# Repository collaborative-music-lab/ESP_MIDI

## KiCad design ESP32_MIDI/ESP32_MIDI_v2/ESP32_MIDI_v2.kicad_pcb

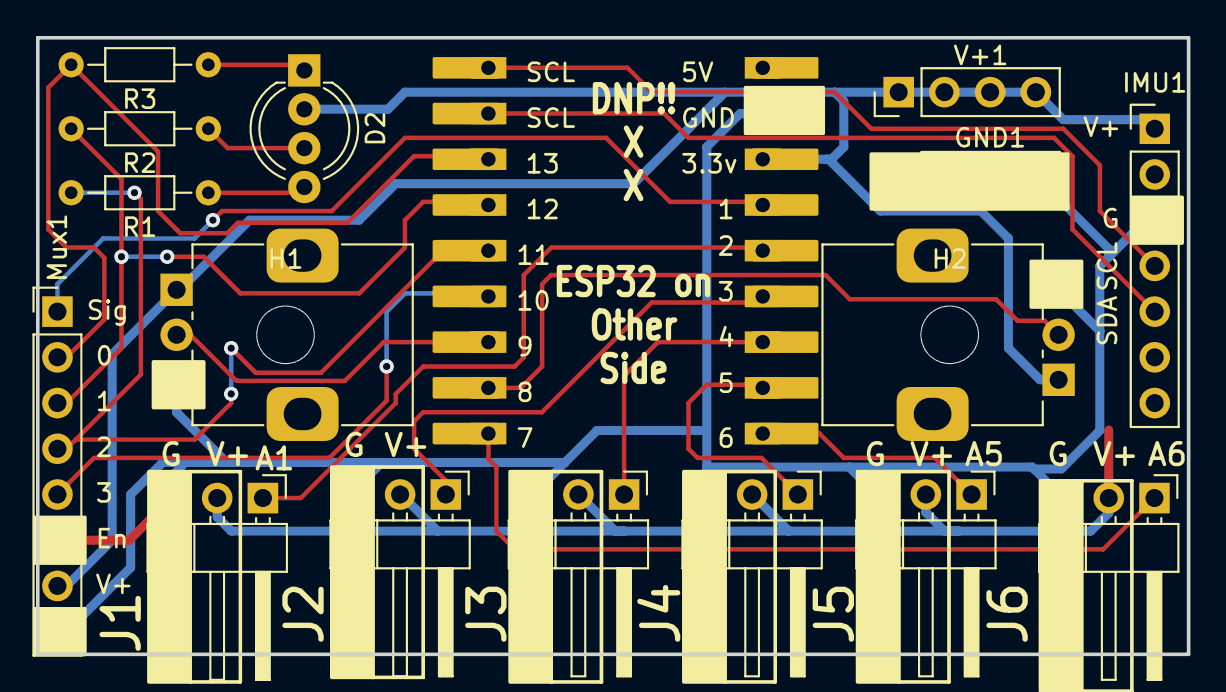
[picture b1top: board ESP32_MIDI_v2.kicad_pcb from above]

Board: 2 copper layers, 63.9 x 34.3 mm, 19 parts (1 on the bottom side), 20 nets.

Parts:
D2: LED_RAGB; LED_D5.0mm-4_RGB_Wide_Pins
GND1: Conn_01x04_Pin; PinHeader_1x04_P2.54mm_Vertical
H1, H2: MountingHole; MountingHole_3.2mm_M3
IMU1: Conn_01x07_Pin; PinHeader_1x07_P2.54mm_Vertical
J1, J2, J3, J4, J5, J6: Conn_01x03_Pin; PinHeader_1x03_P2.54mm_Horizontal
Mux1: Conn_01x08_Pin; PinHeader_1x08_P2.54mm_Vertical
R1, R2, R3: R; R_Axial_DIN0204_L3.6mm_D1.6mm_P7.62mm_Horizontal
RV1, RV2: R_Potentiometer; Potentiometer_Alps_RK09K_Single_Vertical
U2: Wifiduino-ESP32S3
V+1: Conn_01x04_Pin; PinHeader_1x04_P2.54mm_Vertical

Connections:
+3.3V: D2.2 (A), IMU1.1, J1.2, J2.2, J3.2, J4.2, J5.2, J6.2, Mux1.7, RV1.1, RV2.1, U2.3 (3V3), V+1.1, V+1.2, V+1.3, V+1.4
/A0: Mux1.1, U2.4 (GPIO1/ADC1_CH0)
/A1: J1.1, U2.5 (GPIO2/ADC1_CH1)
/A2: J2.1, U2.6 (GPIO3/ADC1_CH2)
/A3: J3.1, U2.7 (GPIO4/ADC1_CH3)
/A4: J4.1, U2.8 (GPIO5/ADC1_CH4)
/A5: J5.1, U2.9 (GPIO6/ADC1_CH5)
/A6: J6.1, U2.10 (GPIO7/ADC1_CH6)
/A7: RV2.2, U2.11 (GPIO8/ADC1_CH7)
/A8: RV1.2, U2.12 (GPIO9/ADC1_CH8)
/A9: Mux1.5, U2.13 (GPIO10/ADC1_CH9)
/D0: Mux1.4, R1.2, U2.14 (GPIO11/ADC2_CH0)
/D1: Mux1.3, R2.2, U2.15 (GPIO12/ADC2_CH1)
/D2: Mux1.2, R3.2, U2.16 (GPIO13/ADC2_CH2)
/SCL: IMU1.4, U2.18 (GPIO43/U0TXD)
/SDA: IMU1.5, U2.17 (GPIO44/U0RXD)
GND: GND1.1, GND1.2, GND1.3, GND1.4, IMU1.3, J1.3, J2.3, J3.3, J4.3, J5.3, J6.3, Mux1.6, Mux1.8, RV1.3, RV2.3, U2.2 (GND)
unnamed: D2.4 (BK), R1.1
unnamed: D2.3 (GK), R2.1
unnamed: D2.1 (RK), R3.1

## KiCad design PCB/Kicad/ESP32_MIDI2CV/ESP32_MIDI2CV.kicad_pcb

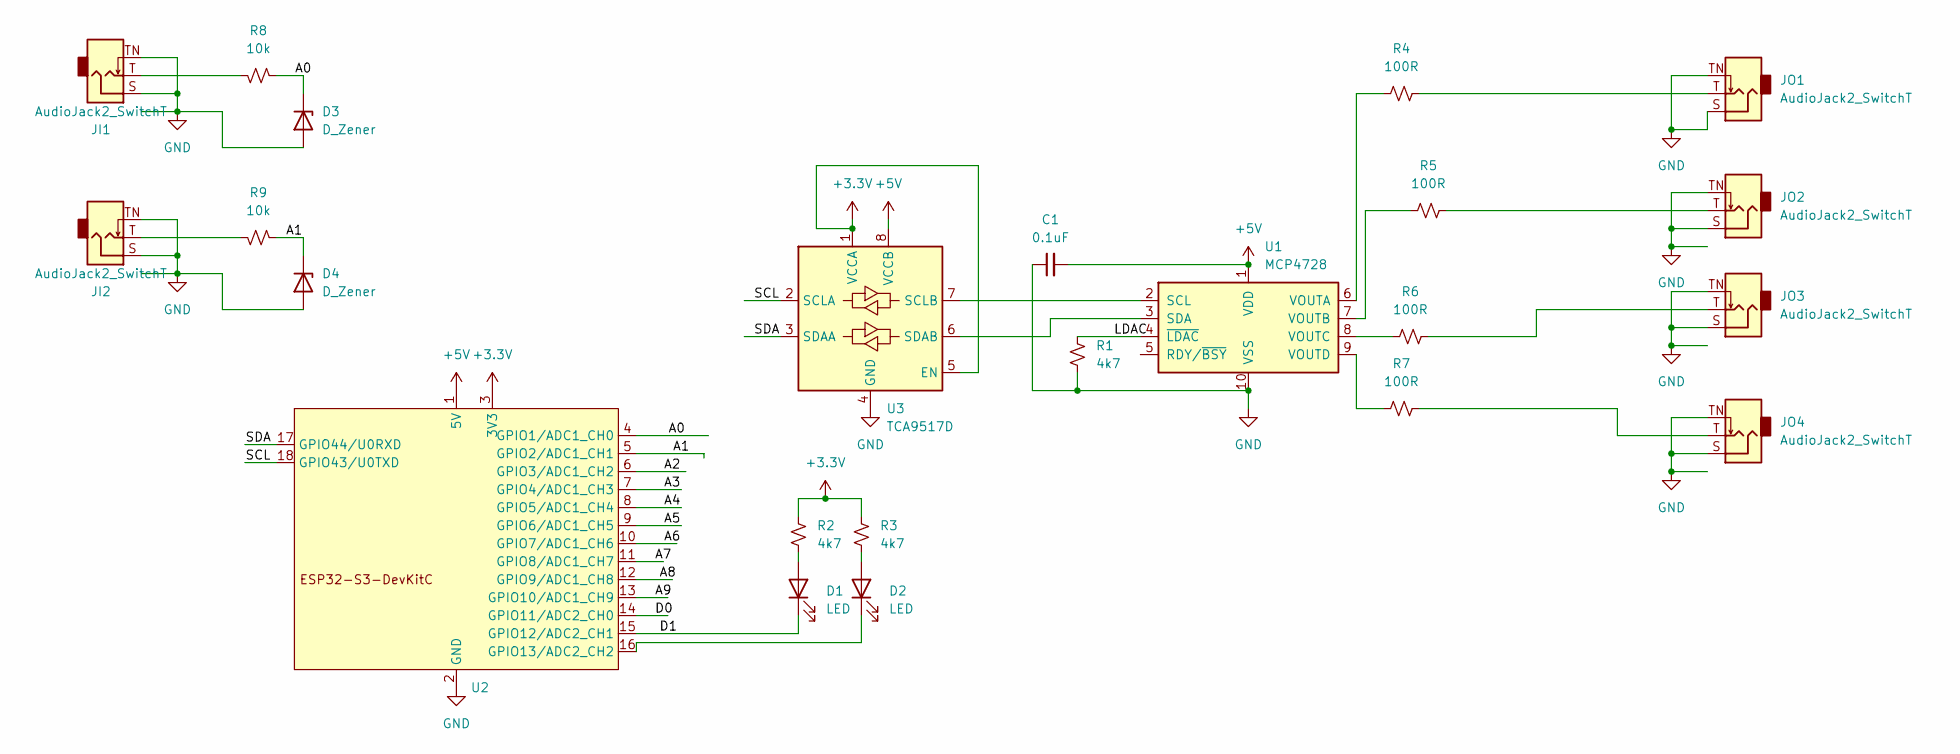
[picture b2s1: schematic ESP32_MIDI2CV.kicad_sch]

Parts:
C1: 0.1uF; C_Disc_D6.0mm_W2.5mm_P5.00mm
D1, D2: LED; LED_D3.0mm
D3, D4: D_Zener; D_DO-35_SOD27_P7.62mm_Horizontal
JI1, JI2: AudioJack2_SwitchT; Jack_3.5mm_QingPu_WQP-PJ398SM_Vertical_CircularHoles
JO1, JO2, JO3, JO4: AudioJack2_SwitchT; Jack_3.5mm_QingPu_WQP-PJ398SM_Vertical_CircularHoles
R1, R2, R3: 4k7; R_0805_2012Metric
R4, R5, R6, R7: 100R; R_0805_2012Metric
R8, R9: 10k; R_0805_2012Metric
U1: MCP4728; MSOP-10_3x3mm_P0.5mm
U2: Wifiduino-ESP32S3-SMD
U3: TCA9517D; SOIC-8_3.9x4.9mm_P1.27mm

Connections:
+3.3V: R2.1, R3.1, U2.3 (3V3), U3.1 (VCCA), U3.5 (EN)
+5V: C1.2, U1.1 (VDD), U2.1 (5V), U3.8 (VCCB)
/A0: D3.1 (K), R8.1, U2.4 (GPIO1/ADC1_CH0)
/A1: D4.1 (K), R9.1, U2.5 (GPIO2/ADC1_CH1)
/A2: U2.6 (GPIO3/ADC1_CH2)
/A3: U2.7 (GPIO4/ADC1_CH3)
/A4: U2.8 (GPIO5/ADC1_CH4)
/A5: U2.9 (GPIO6/ADC1_CH5)
/A6: U2.10 (GPIO7/ADC1_CH6)
/A7: U2.11 (GPIO8/ADC1_CH7)
/A8: U2.12 (GPIO9/ADC1_CH8)
/A9: U2.13 (GPIO10/ADC1_CH9)
/D0: U2.14 (GPIO11/ADC2_CH0)
/D1: D1.1 (K), U2.15 (GPIO12/ADC2_CH1)
/LDAC: R1.1, U1.4 (~LDAC)
/SCL: U2.18 (GPIO43/U0TXD), U3.2 (SCLA)
/SDA: U2.17 (GPIO44/U0RXD), U3.3 (SDAA)
GND: C1.1, D3.2 (A), D4.2 (A), JI1.S, JI1.TN, JI2.S, JI2.TN, JO1.S, JO1.TN, JO2.S, JO2.TN, JO3.S, JO3.TN, JO4.S, JO4.TN, R1.2, U1.10 (VSS), U2.2 (GND), U3.4 (GND)
unnamed: D1.2 (A), R2.2
unnamed: D2.2 (A), R3.2
unnamed: D2.1 (K), U2.16 (GPIO13/ADC2_CH2)
unnamed: JI1.T, R8.2
unnamed: JI2.T, R9.2
unnamed: JO1.T, R4.2
unnamed: JO2.T, R5.2
unnamed: JO3.T, R6.2
unnamed: JO4.T, R7.2
unnamed: U1.2 (SCL), U3.7 (SCLB)
unnamed: U1.3 (SDA), U3.6 (SDAB)
unnamed: R4.1, U1.6 (VOUTA)
unnamed: R5.1, U1.7 (VOUTB)
unnamed: R6.1, U1.8 (VOUTC)
unnamed: R7.1, U1.9 (VOUTD)

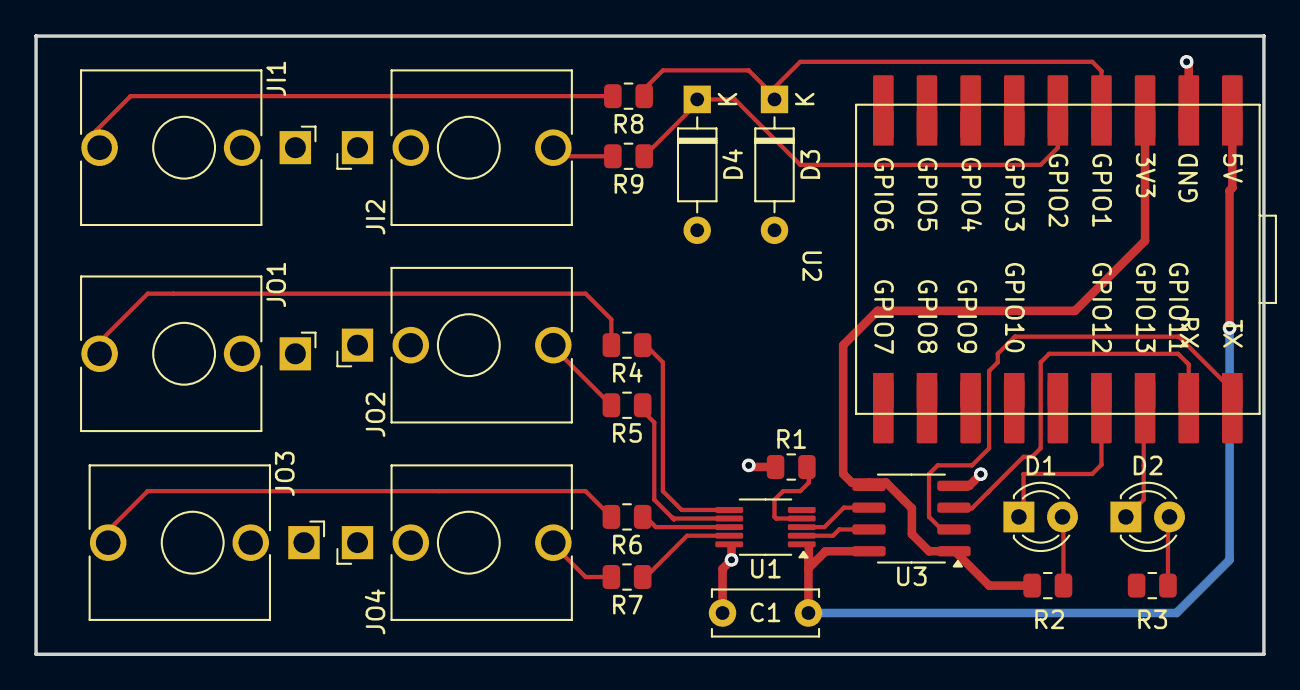
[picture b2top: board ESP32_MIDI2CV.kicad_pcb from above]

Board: 2 copper layers, 71.5 x 36.0 mm, 23 parts (0 on the bottom side), 24 nets.

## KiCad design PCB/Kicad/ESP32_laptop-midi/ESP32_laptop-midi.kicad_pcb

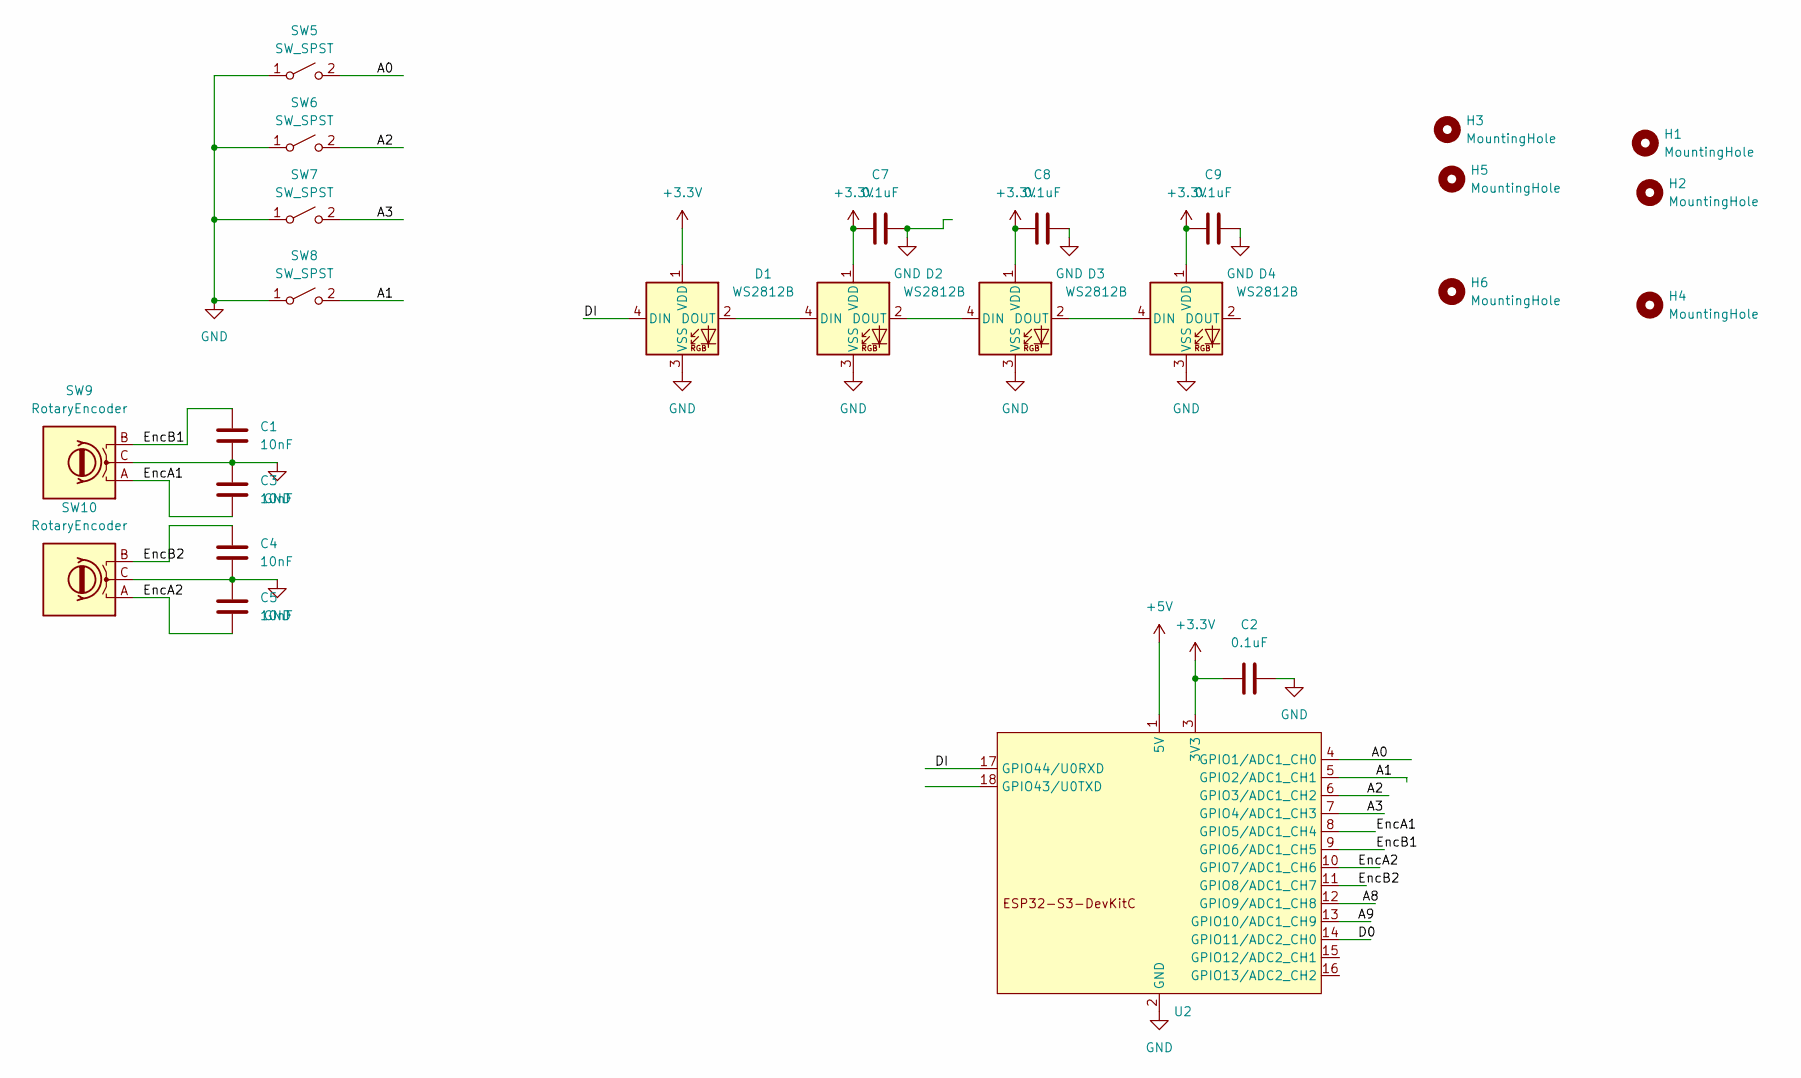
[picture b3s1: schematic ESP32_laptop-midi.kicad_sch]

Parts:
C1, C3, C4, C5: 10nF; C_0805_2012Metric_Pad1.18x1.45mm_HandSolder
C2, C7, C8, C9: 0.1uF; C_0805_2012Metric_Pad1.18x1.45mm_HandSolder
D1, D2, D3, D4: WS2812B; LED_WS2812B_PLCC4_5.0x5.0mm_P3.2mm
H1, H2, H3, H4, H5, H6: MountingHole; MountingHole_3.2mm_M3
SW5, SW6, SW7, SW8: SW_SPST; SW_Cherry_MX_1.00u_PCB
SW9, SW10: RotaryEncoder; EC10E1220505_AAL
U2: Wifiduino-ESP32S3-SMD

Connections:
+3.3V: C2.2, C7.2, C8.2, C9.2, D1.1 (VDD), D2.1 (VDD), D3.1 (VDD), D4.1 (VDD), U2.3 (3V3)
+5V: U2.1 (5V)
/A0: SW5.2 (B), U2.4 (GPIO1/ADC1_CH0)
/A1: SW8.2 (B), U2.5 (GPIO2/ADC1_CH1)
/A2: SW6.2 (B), U2.6 (GPIO3/ADC1_CH2)
/A3: SW7.2 (B), U2.7 (GPIO4/ADC1_CH3)
/A8: U2.12 (GPIO9/ADC1_CH8)
/A9: U2.13 (GPIO10/ADC1_CH9)
/D0: U2.14 (GPIO11/ADC2_CH0)
/DI: D1.4 (DIN), U2.17 (GPIO44/U0RXD)
/EncA1: C3.2, SW9.A, U2.8 (GPIO5/ADC1_CH4)
/EncA2: C5.2, SW10.A, U2.10 (GPIO7/ADC1_CH6)
/EncB1: C1.1, SW9.B, U2.9 (GPIO6/ADC1_CH5)
/EncB2: C4.1, SW10.B, U2.11 (GPIO8/ADC1_CH7)
GND: C1.2, C2.1, C3.1, C4.2, C5.1, C7.1, C8.1, C9.1, D1.3 (VSS), D2.3 (VSS), D3.3 (VSS), D4.3 (VSS), SW5.1 (A), SW6.1 (A), SW7.1 (A), SW8.1 (A), SW9.C, SW10.C, U2.2 (GND)
unnamed: D1.2 (DOUT), D2.4 (DIN)
unnamed: D2.2 (DOUT), D3.4 (DIN)
unnamed: D3.2 (DOUT), D4.4 (DIN)

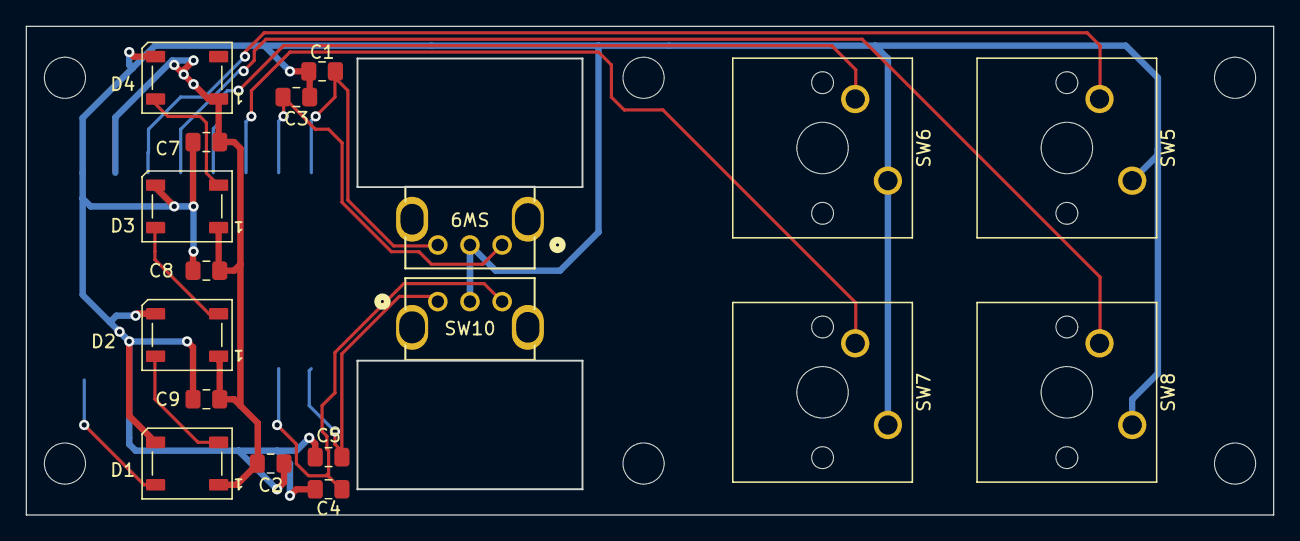
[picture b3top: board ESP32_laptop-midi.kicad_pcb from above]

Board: 2 copper layers, 97.0 x 38.0 mm, 25 parts (1 on the bottom side), 14 nets.

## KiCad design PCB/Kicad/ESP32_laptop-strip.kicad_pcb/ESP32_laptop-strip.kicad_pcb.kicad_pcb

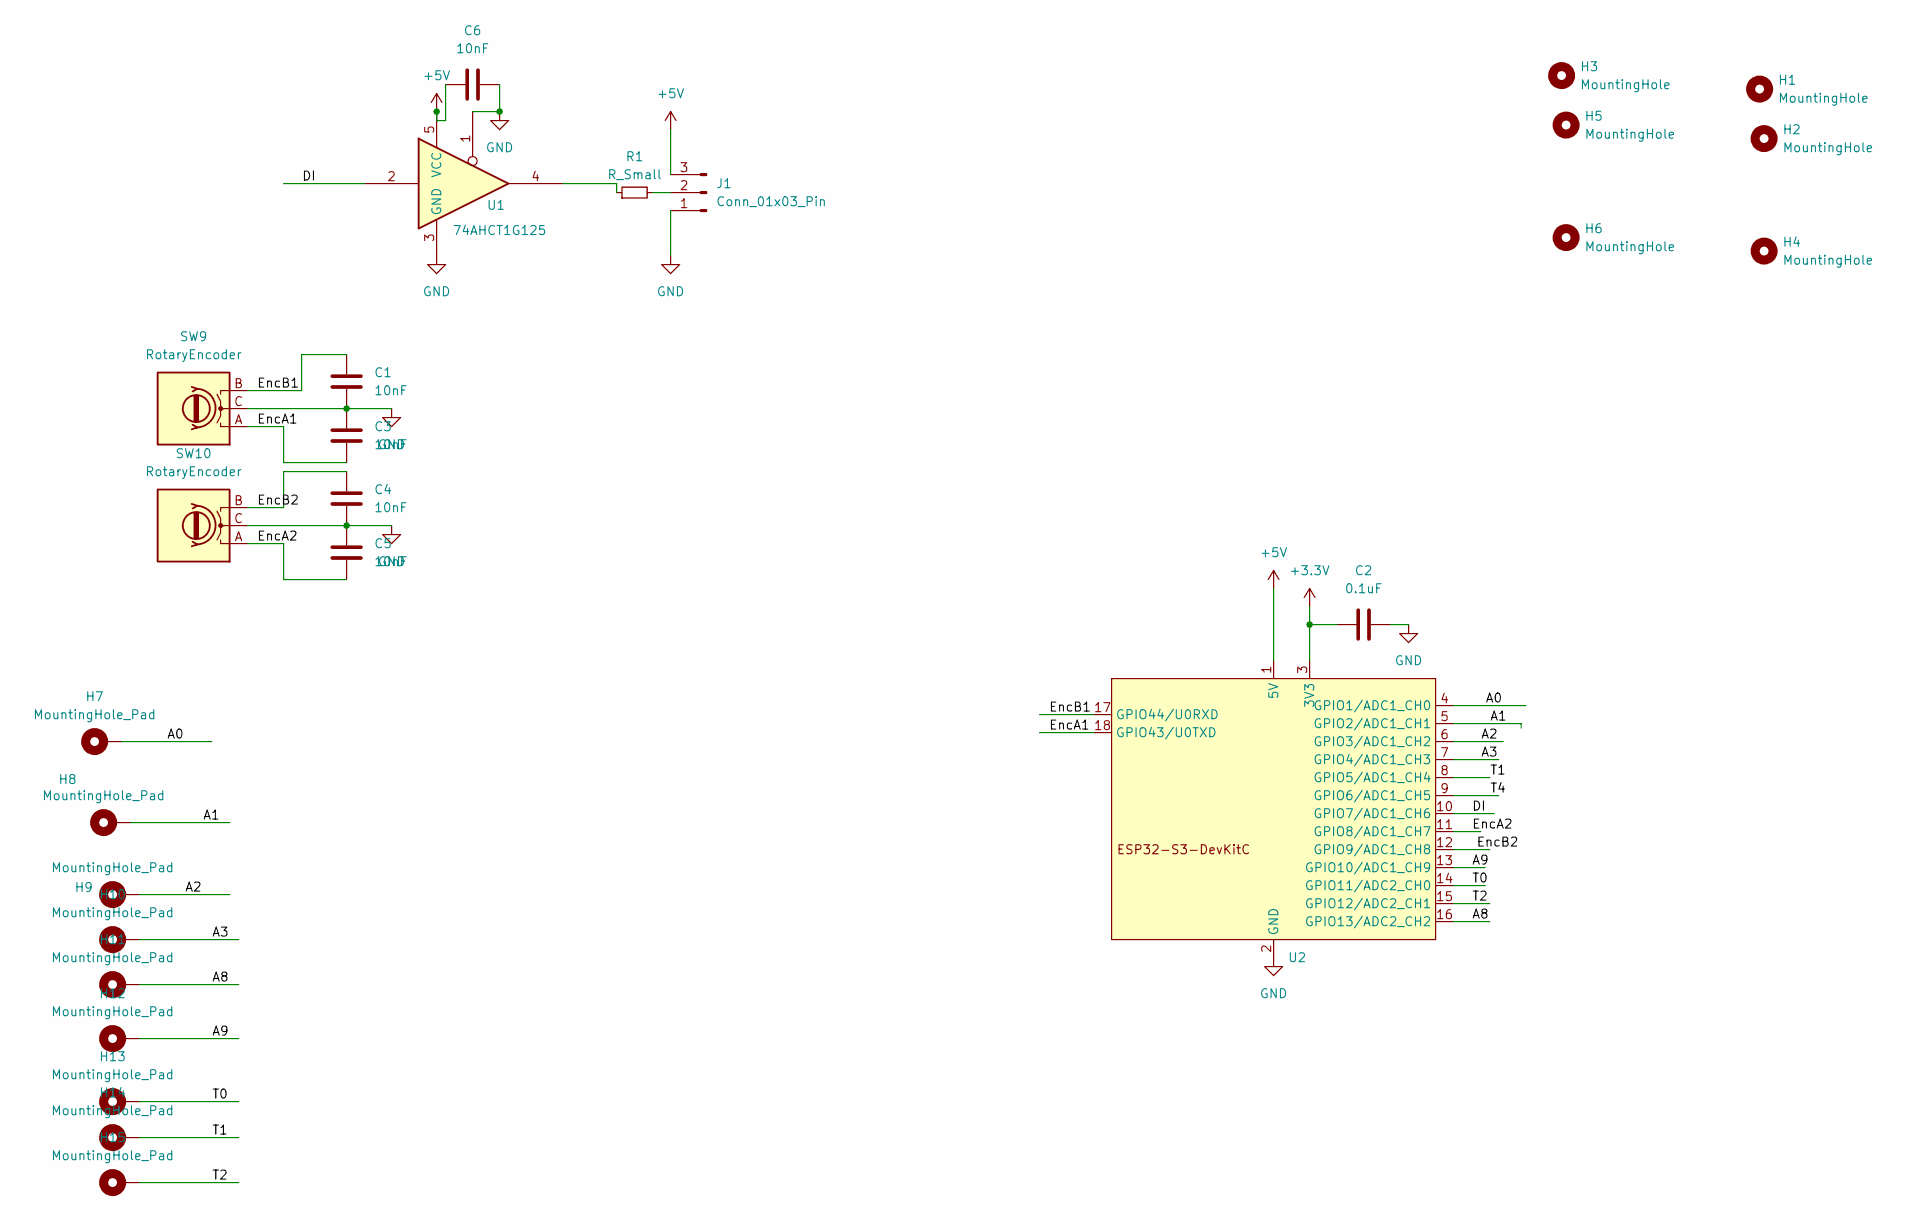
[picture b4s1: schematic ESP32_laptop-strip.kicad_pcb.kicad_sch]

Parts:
C1, C3, C4, C5, C6: 10nF; C_0805_2012Metric_Pad1.18x1.45mm_HandSolder
C2: 0.1uF; C_0805_2012Metric_Pad1.18x1.45mm_HandSolder
H1, H2, H3, H4, H5, H6: MountingHole; MountingHole_3.2mm_M3
H7, H8, H9, H10, H11, H12, H13, H14, H15: MountingHole_Pad; MountingHole_4.3mm_M4_DIN965_Pad
J1: Conn_01x03_Pin; WS2812_PADS
R1: R_Small; R_0805_2012Metric_Pad1.20x1.40mm_HandSolder
SW9, SW10: RotaryEncoder; RotaryEncoder_Vertical_10mm
U1: 74AHCT1G125; TSOT-23-5_HandSoldering
U2: Wifiduino-ESP32S3-SMD

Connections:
+3.3V: C2.2, U2.3 (3V3)
+5V: C6.1, J1.3, U1.5 (VCC), U2.1 (5V)
/A0: H7.1, U2.4 (GPIO1/ADC1_CH0)
/A1: H8.1, U2.5 (GPIO2/ADC1_CH1)
/A2: H9.1, U2.6 (GPIO3/ADC1_CH2)
/A3: H10.1, U2.7 (GPIO4/ADC1_CH3)
/A8: H11.1, U2.16 (GPIO13/ADC2_CH2)
/A9: H12.1, U2.13 (GPIO10/ADC1_CH9)
/DI: U1.2, U2.10 (GPIO7/ADC1_CH6)
/EncA1: C3.2, SW9.A, U2.18 (GPIO43/U0TXD)
/EncA2: C5.2, SW10.A, U2.11 (GPIO8/ADC1_CH7)
/EncB1: C1.1, SW9.B, U2.17 (GPIO44/U0RXD)
/EncB2: C4.1, SW10.B, U2.12 (GPIO9/ADC1_CH8)
/T0: H13.1, U2.14 (GPIO11/ADC2_CH0)
/T1: H14.1, U2.8 (GPIO5/ADC1_CH4)
/T2: H15.1, U2.15 (GPIO12/ADC2_CH1)
/T4: U2.9 (GPIO6/ADC1_CH5)
GND: C1.2, C2.1, C3.1, C4.2, C5.1, C6.2, J1.1, SW9.C, SW10.C, U1.1, U1.3 (GND), U2.2 (GND)
unnamed: J1.2, R1.2
unnamed: R1.1, U1.4

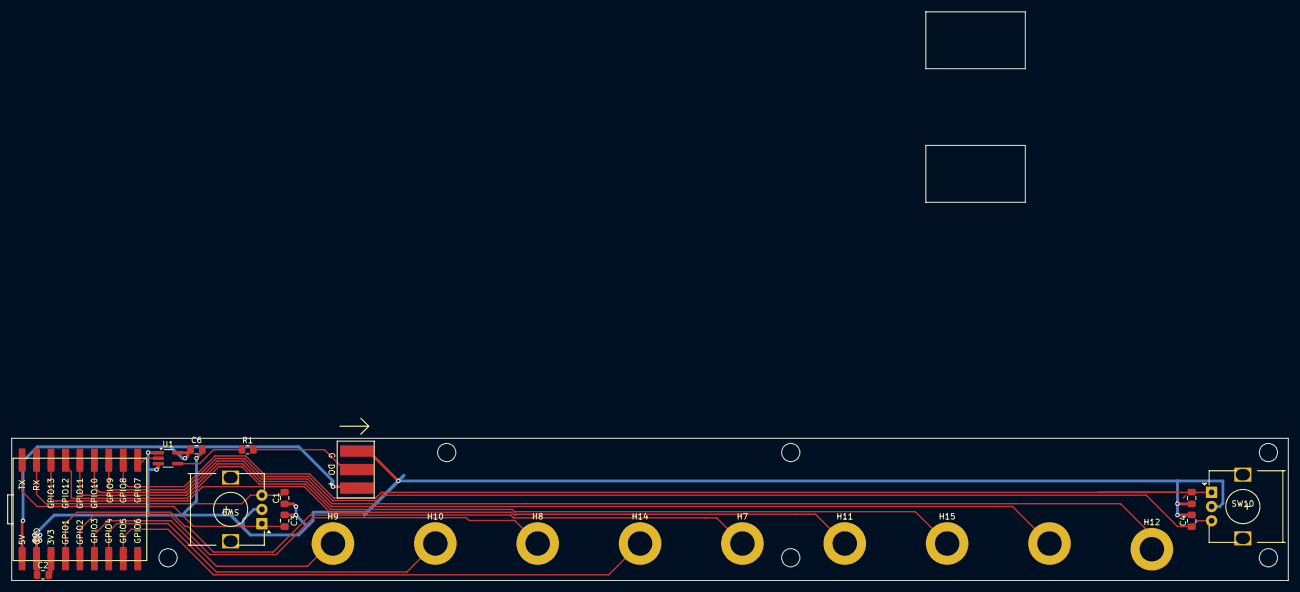
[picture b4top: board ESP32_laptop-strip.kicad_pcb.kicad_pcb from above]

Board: 2 copper layers, 224.5 x 25.0 mm, 27 parts (0 on the bottom side), 19 nets.

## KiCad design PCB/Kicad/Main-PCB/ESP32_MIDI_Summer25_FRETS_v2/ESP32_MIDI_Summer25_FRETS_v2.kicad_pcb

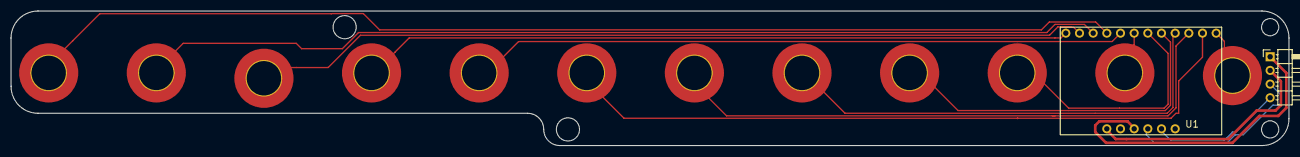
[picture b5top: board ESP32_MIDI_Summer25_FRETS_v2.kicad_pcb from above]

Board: 2 copper layers, 237.5 x 25.0 mm, 18 parts (0 on the bottom side), 16 nets.

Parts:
H1, H2: MountingHole; MountingHole_4.3mm_M4
H3, H7, H8, H11, H12, H13, H14, H15, H16, H17, H18, H19: MountingHole_Pad; MountingHole_6.4mm_M6_DIN965_Pad_TopBottom
H9, H10: MountingHole; MountingHole_3.2mm_M3
J1: Conn_01x04_Pin; PinHeader_1x04_P2.54mm_Horizontal
U1: MPR121_Breakout

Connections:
+3.3V: J1.2, U1.1 (VIN)
/SCL: J1.3, U1.4 (SDA)
/SDA: J1.4, U1.5 (ADD)
/p0: H19.1, U1.7 (T0)
/p1: H13.1, U1.8 (T1)
/p2: H14.1, U1.9 (T2)
/p3: H15.1, U1.10 (T3)
/p4: H16.1, U1.11 (T4)
/p5: H17.1, U1.12 (T5)
/p6: H18.1, U1.13 (T6)
/p7: H12.1, U1.14 (T7)
/p8: H3.1, U1.15 (T8)
/p9: H8.1, U1.16 (T9)
/p10: H7.1, U1.17 (T10)
/p11: H11.1, U1.18 (T11)
GND: J1.1, U1.3 (SCL)
